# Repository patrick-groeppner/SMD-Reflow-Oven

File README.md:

# SMD-Reflow-Oven
files and pictures for the selfmade SMD reflow oven. Made with an Arduino as a PID controller, a thermocouple sensor for fast and high range measurements and a solid state relay for switching an mini oven on and off

capable of:
- reflow soldering with different profiles / manual set temperature
- heating pcb clads with photoresist lacquer: temp curve and manual set temperature

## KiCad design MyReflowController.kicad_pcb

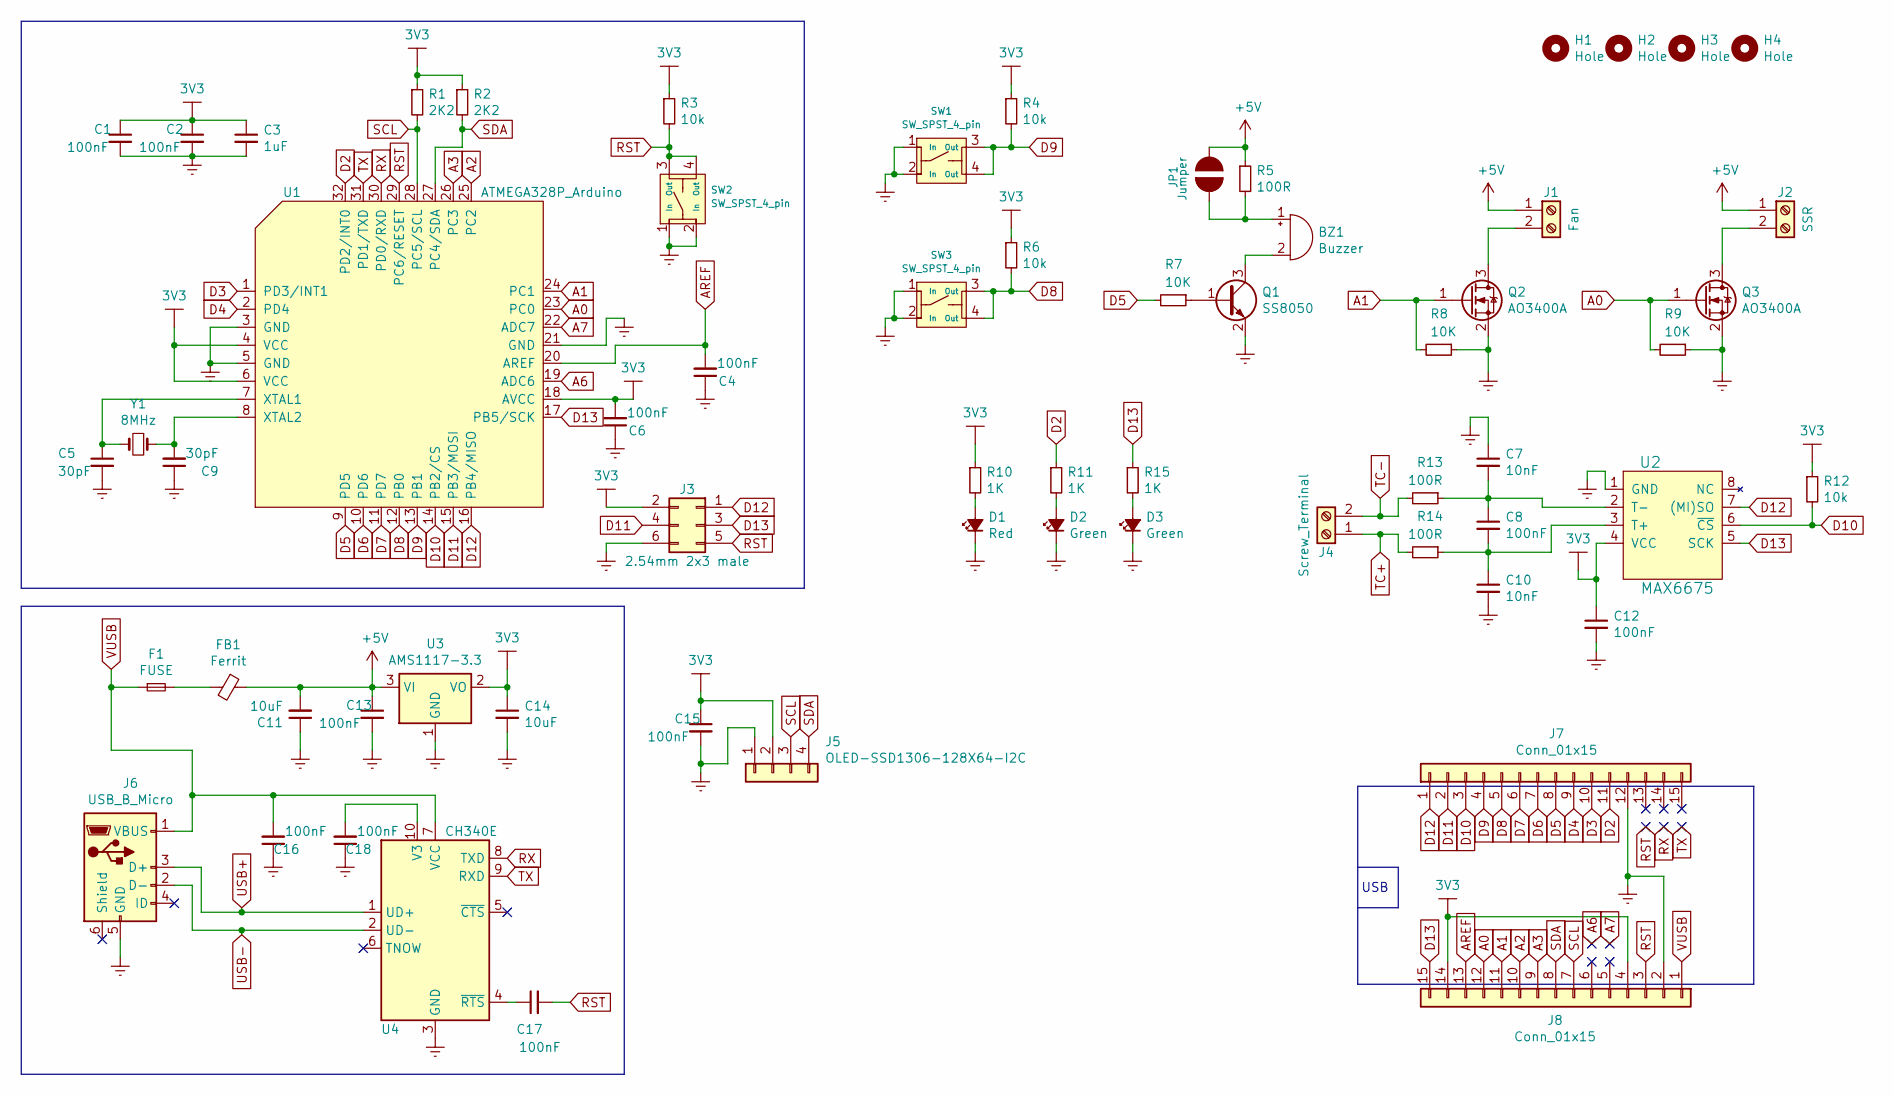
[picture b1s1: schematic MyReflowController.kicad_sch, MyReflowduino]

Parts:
BZ1: Buzzer; Buzzer_12x9.5RM7.6
C1, C2, C4, C6, C8, C12, C13, C15, C16, C18: 100nF; C_0603_1608Metric_Pad1.08x0.95mm_HandSolder; Part# C14663
C3: 1uF; C_0805_2012Metric_Pad1.18x1.45mm_HandSolder; Part# C28323
C5, C9: 30pF; C_0603_1608Metric; Part# C22397
C7, C10: 10nF; C_0603_1608Metric_Pad1.08x0.95mm_HandSolder; Part# C57112
C11, C14: 10uF; C_0805_2012Metric_Pad1.18x1.45mm_HandSolder; Part# C15850
C17: 100nF; C_0805_2012Metric_Pad1.18x1.45mm_HandSolder; Part# C14663
D1: Red; LED_0805_2012Metric_Pad1.15x1.40mm_HandSolder; Part# C84256
D2, D3: Green; LED_0603_1608Metric_Pad1.05x0.95mm_HandSolder; Part# C72043
F1: FUSE; Fuse_1206_3216Metric_Pad1.42x1.75mm_HandSolder
FB1: Ferrit; Fuse_0805_2012Metric_Pad1.15x1.40mm_HandSolder; Part# C1017
H1, H2, H3, H4: Hole; MountingHole_3.2mm_M3
J1: Fan; TerminalBlock_bornier-2_P5.08mm
J2: SSR; TerminalBlock_bornier-2_P5.08mm
J3: 2.54mm 2x3 male; PinSocket_2x03_P2.54mm_Vertical
J4: Screw_Terminal; TerminalBlock_bornier-2_P5.08mm
J5: OLED-SSD1306-128X64-I2C; OLED-SSD1306-128X64-THT
J6: USB_B_Micro; 111A1010D10200_USB-2.0_THT
J7, J8: Conn_01x15; PinHeader_1x15_P2.54mm_Vertical
JP1: Jumper; SolderJumper-2_P1.3mm_Bridged_Pad1.0x1.5mm
Q1: SS8050; SOT-23-3; Part# C2150
Q2, Q3: AO3400A; SOT-23; Part# C20917
R1, R2: 2K2; R_0603_1608Metric_Pad0.98x0.95mm_HandSolder; Part# C4190
R3, R4, R6, R12: 10k; R_0805_2012Metric_Pad1.20x1.40mm_HandSolder; Part# C17414
R5: 100R; R_1206_3216Metric_Pad1.30x1.75mm_HandSolder; Part# C17901
R7, R8, R9: 10K; R_1206_3216Metric_Pad1.30x1.75mm_HandSolder; Part# C17902
R10, R11, R15: 1K; R_0603_1608Metric_Pad0.98x0.95mm_HandSolder; Part# C21190
R13, R14: 100R; R_0603_1608Metric; Part# C22775
SW1, SW2, SW3: SW_SPST_4_pin; TACTILE_SWITCH_PTH_6.0MM
U1: ATMEGA328P_Arduino; TQFP-32_7x7mm; Part# C14877
U2: MAX6675; SOIC-8_W3.9mm; Part# C16030
U3: AMS1117-3.3; SOT-223-3_TabPin2; Part# C6186
U4: CH340E; MSOP-10_3x3mm_P0.5mm; Part# C99652
Y1: 8MHz; Crystal_SMD_TXC_7A-2Pin_5x3.2mm; Part# C115962

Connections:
3V3: C1.1, C2.1, C3.1, C6.2, C12.1, C14.1, C15.1, J3.2, J5.2, J8.4, J8.14, R1.1, R2.1, R3.1, R4.1, R6.1, R10.1, R12.1, U1.4 (VCC), U1.6 (VCC), U1.18 (AVCC), U2.4 (VCC), U3.2 (VO)
+5V: C11.2, C13.1, FB1.1, J1.1, J2.1, JP1.1, R5.1, U3.3 (VI)
A0: J8.12, Q3.1 (G), R9.2, U1.23 (PC0)
A1: J8.11, Q2.1 (G), R8.2, U1.24 (PC1)
A2: J8.10, U1.25 (PC2)
A3: J8.9, U1.26 (PC3)
A6: U1.19 (ADC6)
A7: U1.22 (ADC7)
AREF: C4.2, J8.13, U1.20 (AREF)
D2: J7.11, R11.1, U1.32 (PD2/INT0)
D3: J7.10, U1.1 (PD3/INT1)
D4: J7.9, U1.2 (PD4)
D5: J7.8, R7.2, U1.9 (PD5)
D6: J7.7, U1.10 (PD6)
D7: J7.6, U1.11 (PD7)
D8: J7.5, R6.2, SW3.3 (Out), SW3.4 (Out), U1.12 (PB0)
D9: J7.4, R4.2, SW1.3 (Out), SW1.4 (Out), U1.13 (PB1)
D10: J7.3, R12.2, U1.14 (PB2/CS), U2.6 (~CS)
D11: J3.4, J7.2, U1.15 (PB3/MOSI)
D12: J3.1, J7.1, U1.16 (PB4/MISO), U2.7 ((MI)SO)
D13: J3.3, J8.15, R15.1, U1.17 (PB5/SCK), U2.5 (SCK)
Masse: C1.2, C2.2, C3.2, C4.1, C5.2, C6.1, C7.1, C9.1, C10.2, C11.1, C12.2, C13.2, C14.2, C15.2, C16.1, C18.1, D1.1 (K), D2.1 (K), D3.1 (K), J3.6, J5.1, J6.5 (GND), J7.12, J8.2, Q1.2 (E), Q2.2 (S), Q3.2 (S), R8.1, R9.1, SW1.1 (In), SW1.2 (In), SW2.1 (In), SW2.2 (In), SW3.1 (In), SW3.2 (In), U1.3 (GND), U1.5 (GND), U1.21 (GND), U2.1 (GND), U3.1 (GND), U4.3 (GND)
unnamed: BZ1.1 (-), JP1.2, R5.2
unnamed: BZ1.2 (+), Q1.3 (C)
unnamed: C5.1, U1.7 (XTAL1), Y1.2
unnamed: C7.2, C8.1, R13.1, U2.2 (T-)
unnamed: C9.2, U1.8 (XTAL2), Y1.1
unnamed: C8.2, C10.1, R14.1, U2.3 (T+)
unnamed: C17.1, U4.4 (~RTS)
unnamed: C18.2, U4.10 (V3)
unnamed: D1.2 (A), R10.2
unnamed: D2.2 (A), R11.2
unnamed: D3.2 (A), R15.2
unnamed: F1.2, FB1.2
unnamed: J1.2, Q2.3 (D)
unnamed: J2.2, Q3.3 (D)
unnamed: Q1.1 (B), R7.1
RST: C17.2, J3.5, J8.3, R3.2, SW2.3 (Out), SW2.4 (Out), U1.29 (PC6/RESET)
RX: U1.30 (PD0/RXD), U4.8 (TXD)
SCL: J5.3, J8.7, R1.2, U1.28 (PC5/SCL)
SDA: J5.4, J8.8, R2.2, U1.27 (PC4/SDA)
TC+: J4.1, R14.2
TC-: J4.2, R13.2
TX: U1.31 (PD1/TXD), U4.9 (RXD)
USB+: J6.3 (D+), U4.1 (UD+)
USB-: J6.2 (D-), U4.2 (UD-)
VUSB: C16.2, F1.1, J6.1 (VBUS), J8.1, U4.7 (VCC)

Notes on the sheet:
USB

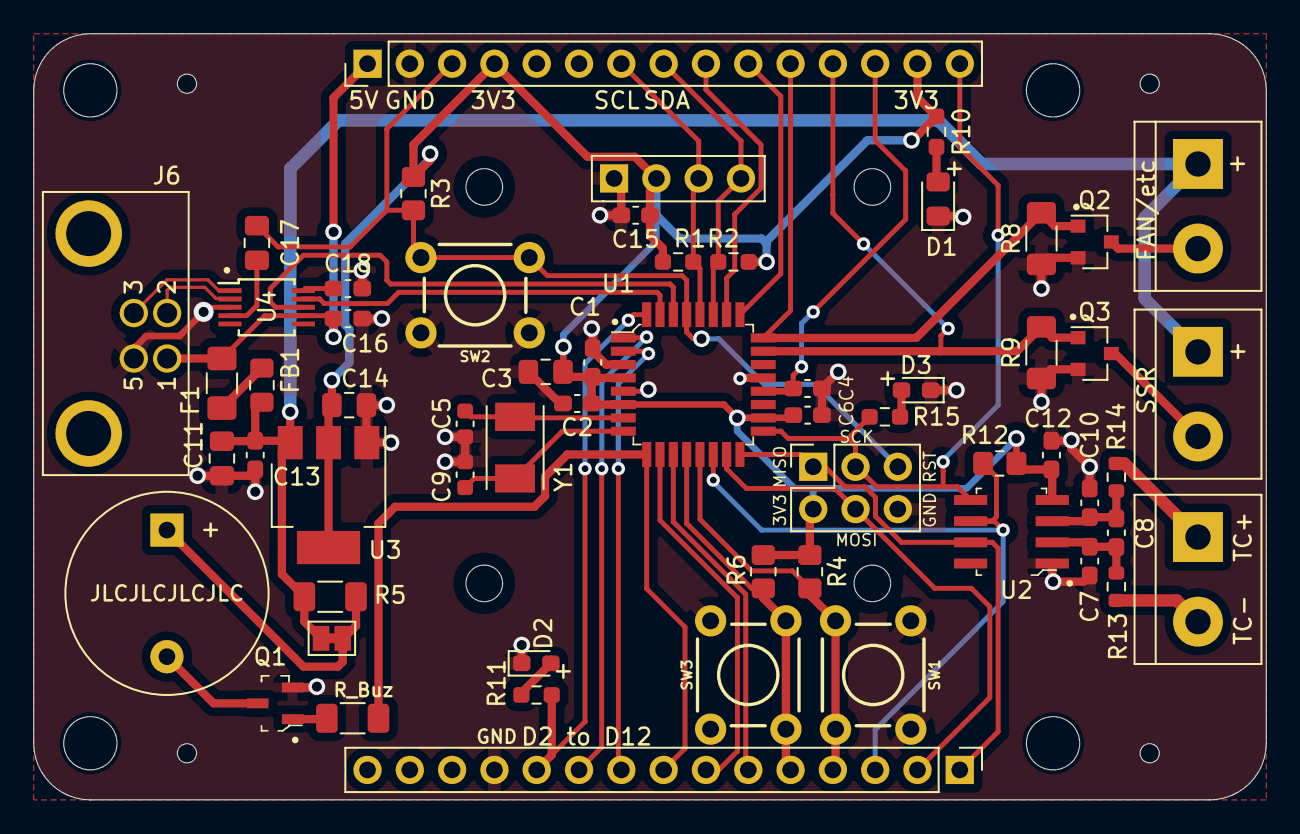
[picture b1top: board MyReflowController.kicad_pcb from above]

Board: 2 copper layers, 74.0 x 46.0 mm, 63 parts (0 on the bottom side), 45 nets.
